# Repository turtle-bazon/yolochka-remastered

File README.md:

# Yolochka Remastered

Yolochka Remastered is a 36 keys (3x5 + 3 thumbs per hand) row staggered keyboard, inspired by [Aroum's YOLOCHKA](https://github.com/aroum/yolochka). It started as an attempt to turn the original YOLOCHKA into a PCB-based design.

## Images

## PCB Images

## Bill Of Materials

| Item                       | Quantity | Remarks                                                   |
| ---------------------------|----------| ----------------------------------------------------------|
| NRFproMicro                | 1        | [Link](https://aliexpress.com/item/1005007088422530.html) |
| MX Style Mechanical Switch | 36       | Any green themed colors, but works any, see below         |
| MX HotSwap Socket          | 36       | Any MX Compatible, but green preferred                    |
| SMD Diode 1n4148 SOD123    | 36       | If you can find green or red is good                      |
| SK6812MINI-E               | 41       |                                                           |
| MSK12C02                   | 1        | Power switch                                              |
| EVQP7C01K                  | 1        | Reset switch                                              |
| 14500 li-ion battery       | 2        |                                                           |
| 24 AWG wire                |          | Or something similar                                      |
| M2 threaded insert         | 11       | 3mm, OD 3.2mm                                             |
| M2x4 Countersunk head      | 2        | For led panel                                             |
| M2x10 Countersunk head     | 4        | For PCB                                                   |
| M2x5 Countersunk head      | 7        | For Case                                                  |

## Firmware

My zmk repo is available [here](https://github.com/turtle-bazon/zmk-yolochka-remastered)

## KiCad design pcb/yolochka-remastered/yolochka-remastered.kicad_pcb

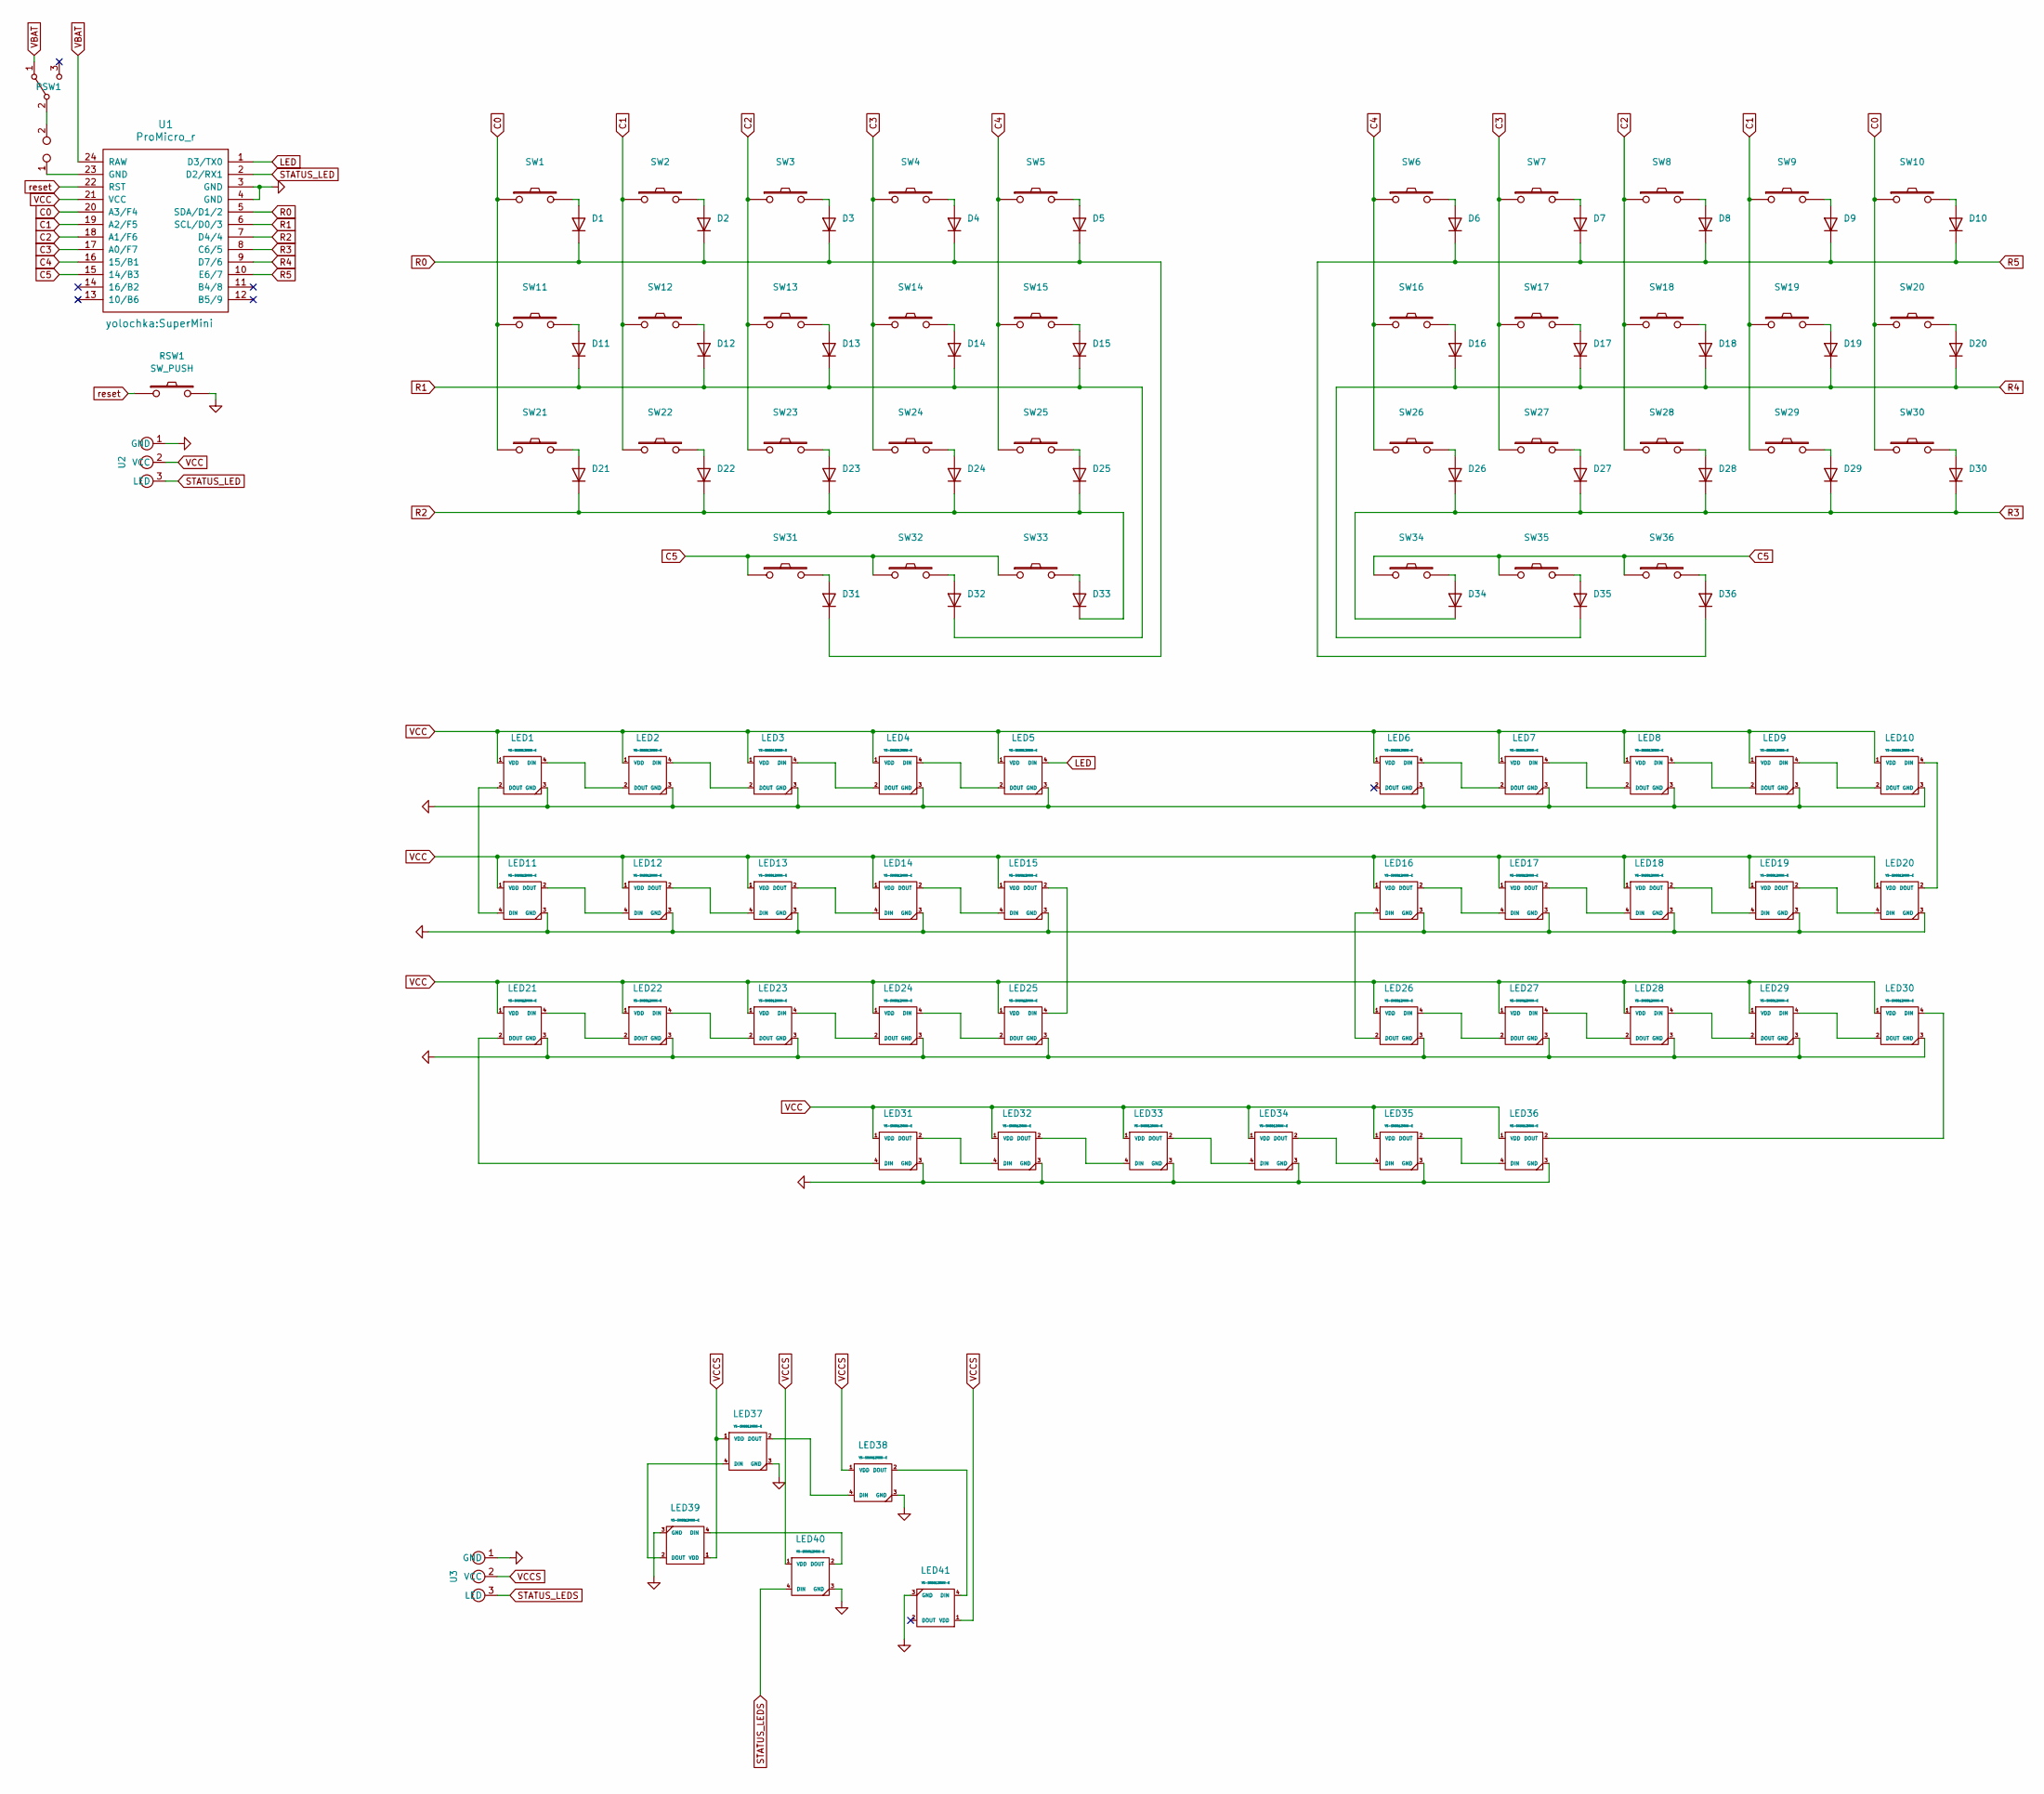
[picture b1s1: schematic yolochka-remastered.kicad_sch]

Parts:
D1, D2, D3, D4, D5, D6, D7, D8, D9, D10, D11, D12, D13, D14, D15, D16, D17, D18, D19, D20, D21, D22, D23, D24, D25, D26, D27, D28, D29, D30, D31, D32, D33, D34, D35, D36: 1N4148; D3_SMD_single
LED1, LED2, LED3, LED4, LED5, LED6, LED7, LED8, LED9, LED10, LED11, LED12, LED13, LED14, LED15, LED16, LED17, LED18, LED19, LED20, LED21, LED22, LED23, LED24, LED25, LED26, LED27, LED28, LED29, LED30, LED31, LED32, LED33, LED34, LED35, LED36, LED37, LED38, LED39, LED40, LED41: YS-SK6812MINI-E; YS-SK6812MINI-E_single
PSW1: SW_SPDT; MSK-12C02
RSW1: SW_PUSH; SW_EVQP7C01K
SW1, SW2, SW3, SW4, SW5, SW6, SW7, SW8, SW9, SW10, SW11, SW12, SW13, SW14, SW15, SW16, SW17, SW18, SW19, SW20, SW21, SW22, SW23, SW24, SW25, SW26, SW27, SW28, SW29, SW30, SW31, SW32, SW33, SW34, SW35, SW36: SW_PUSH; MX-single
TP1: TestPoint_2Pole; battery_conn_duplex
U1: ProMicro_r; SuperMini
U2, U3: rgb3pin

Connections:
C0: SW1.1, SW10.1, SW11.1, SW20.1, SW21.1, SW30.1, U1.20 (A3/F4)
C1: SW2.1, SW9.1, SW12.1, SW19.1, SW22.1, SW29.1, U1.19 (A2/F5)
C2: SW3.1, SW8.1, SW13.1, SW18.1, SW23.1, SW28.1, U1.18 (A1/F6)
C3: SW4.1, SW7.1, SW14.1, SW17.1, SW24.1, SW27.1, U1.17 (A0/F7)
C4: SW5.1, SW6.1, SW15.1, SW16.1, SW25.1, SW26.1, U1.16 (15/B1)
C5: SW31.1, SW32.1, SW33.1, SW34.1, SW35.1, SW36.1, U1.15 (14/B3)
GND: LED1.3 (GND), LED2.3 (GND), LED3.3 (GND), LED4.3 (GND), LED5.3 (GND), LED6.3 (GND), LED7.3 (GND), LED8.3 (GND), LED9.3 (GND), LED10.3 (GND), LED11.3 (GND), LED12.3 (GND), LED13.3 (GND), LED14.3 (GND), LED15.3 (GND), LED16.3 (GND), LED17.3 (GND), LED18.3 (GND), LED19.3 (GND), LED20.3 (GND), LED21.3 (GND), LED22.3 (GND), LED23.3 (GND), LED24.3 (GND), LED25.3 (GND), LED26.3 (GND), LED27.3 (GND), LED28.3 (GND), LED29.3 (GND), LED30.3 (GND), LED31.3 (GND), LED32.3 (GND), LED33.3 (GND), LED34.3 (GND), LED35.3 (GND), LED36.3 (GND), RSW1.2, U1.3 (GND), U1.4 (GND), U2.1 (GND)
GNDS: LED37.3 (GND), LED38.3 (GND), LED39.3 (GND), LED40.3 (GND), LED41.3 (GND), U3.1 (GND)
LED: LED5.4 (DIN), U1.1 (D3/TX0)
unnamed: D1.2 (A), SW1.2
unnamed: D2.2 (A), SW2.2
unnamed: D3.2 (A), SW3.2
unnamed: D4.2 (A), SW4.2
unnamed: D5.2 (A), SW5.2
unnamed: D6.2 (A), SW6.2
unnamed: D7.2 (A), SW7.2
unnamed: D8.2 (A), SW8.2
unnamed: D9.2 (A), SW9.2
unnamed: D10.2 (A), SW10.2
unnamed: D11.2 (A), SW11.2
unnamed: D12.2 (A), SW12.2
unnamed: D13.2 (A), SW13.2
unnamed: D14.2 (A), SW14.2
unnamed: D15.2 (A), SW15.2
unnamed: D16.2 (A), SW16.2
unnamed: D17.2 (A), SW17.2
unnamed: D18.2 (A), SW18.2
unnamed: D19.2 (A), SW19.2
unnamed: D20.2 (A), SW20.2
unnamed: D21.2 (A), SW21.2
unnamed: D22.2 (A), SW22.2
unnamed: D23.2 (A), SW23.2
unnamed: D24.2 (A), SW24.2
unnamed: D25.2 (A), SW25.2
unnamed: D26.2 (A), SW26.2
unnamed: D27.2 (A), SW27.2
unnamed: D28.2 (A), SW28.2
unnamed: D29.2 (A), SW29.2
unnamed: D30.2 (A), SW30.2
unnamed: D31.2 (A), SW31.2
unnamed: D32.2 (A), SW32.2
unnamed: D33.2 (A), SW33.2
unnamed: D34.2 (A), SW34.2
unnamed: D35.2 (A), SW35.2
unnamed: D36.2 (A), SW36.2
unnamed: LED1.4 (DIN), LED2.2 (DOUT)
unnamed: LED1.2 (DOUT), LED11.4 (DIN)
unnamed: LED2.4 (DIN), LED3.2 (DOUT)
unnamed: LED3.4 (DIN), LED4.2 (DOUT)
unnamed: LED4.4 (DIN), LED5.2 (DOUT)
unnamed: LED6.4 (DIN), LED7.2 (DOUT)
unnamed: LED7.4 (DIN), LED8.2 (DOUT)
unnamed: LED8.4 (DIN), LED9.2 (DOUT)
unnamed: LED10.4 (DIN), LED20.2 (DOUT)
unnamed: LED9.4 (DIN), LED10.2 (DOUT)
unnamed: LED11.2 (DOUT), LED12.4 (DIN)
unnamed: LED12.2 (DOUT), LED13.4 (DIN)
unnamed: LED13.2 (DOUT), LED14.4 (DIN)
unnamed: LED14.2 (DOUT), LED15.4 (DIN)
unnamed: LED15.2 (DOUT), LED25.4 (DIN)
unnamed: LED16.4 (DIN), LED26.2 (DOUT)
unnamed: LED16.2 (DOUT), LED17.4 (DIN)
unnamed: LED17.2 (DOUT), LED18.4 (DIN)
unnamed: LED18.2 (DOUT), LED19.4 (DIN)
unnamed: LED19.2 (DOUT), LED20.4 (DIN)
unnamed: LED21.4 (DIN), LED22.2 (DOUT)
unnamed: LED21.2 (DOUT), LED31.4 (DIN)
unnamed: LED22.4 (DIN), LED23.2 (DOUT)
unnamed: LED23.4 (DIN), LED24.2 (DOUT)
unnamed: LED24.4 (DIN), LED25.2 (DOUT)
unnamed: LED26.4 (DIN), LED27.2 (DOUT)
unnamed: LED27.4 (DIN), LED28.2 (DOUT)
unnamed: LED28.4 (DIN), LED29.2 (DOUT)
unnamed: LED29.4 (DIN), LED30.2 (DOUT)
unnamed: LED30.4 (DIN), LED36.2 (DOUT)
unnamed: LED31.2 (DOUT), LED32.4 (DIN)
unnamed: LED32.2 (DOUT), LED33.4 (DIN)
unnamed: LED33.2 (DOUT), LED34.4 (DIN)
unnamed: LED34.2 (DOUT), LED35.4 (DIN)
unnamed: LED35.2 (DOUT), LED36.4 (DIN)
unnamed: LED37.4 (DIN), LED39.2 (DOUT)
unnamed: LED37.2 (DOUT), LED38.4 (DIN)
unnamed: LED38.2 (DOUT), LED41.4 (DIN)
unnamed: LED39.4 (DIN), LED40.2 (DOUT)
unnamed: PSW1.2 (B), TP1.2
unnamed: TP1.1, U1.23 (GND)
R0: D1.1 (K), D2.1 (K), D3.1 (K), D4.1 (K), D5.1 (K), D31.1 (K), U1.5 (SDA/D1/2)
R1: D11.1 (K), D12.1 (K), D13.1 (K), D14.1 (K), D15.1 (K), D32.1 (K), U1.6 (SCL/D0/3)
R2: D21.1 (K), D22.1 (K), D23.1 (K), D24.1 (K), D25.1 (K), D33.1 (K), U1.7 (D4/4)
R3: D26.1 (K), D27.1 (K), D28.1 (K), D29.1 (K), D30.1 (K), D34.1 (K), U1.8 (C6/5)
R4: D16.1 (K), D17.1 (K), D18.1 (K), D19.1 (K), D20.1 (K), D35.1 (K), U1.9 (D7/6)
R5: D6.1 (K), D7.1 (K), D8.1 (K), D9.1 (K), D10.1 (K), D36.1 (K), U1.10 (E6/7)
STATUS_LED: U1.2 (D2/RX1), U2.3 (LED)
STATUS_LEDS: LED40.4 (DIN), U3.3 (LED)
VBAT: PSW1.1 (A), U1.24 (RAW)
VCC: LED1.1 (VDD), LED2.1 (VDD), LED3.1 (VDD), LED4.1 (VDD), LED5.1 (VDD), LED6.1 (VDD), LED7.1 (VDD), LED8.1 (VDD), LED9.1 (VDD), LED10.1 (VDD), LED11.1 (VDD), LED12.1 (VDD), LED13.1 (VDD), LED14.1 (VDD), LED15.1 (VDD), LED16.1 (VDD), LED17.1 (VDD), LED18.1 (VDD), LED19.1 (VDD), LED20.1 (VDD), LED21.1 (VDD), LED22.1 (VDD), LED23.1 (VDD), LED24.1 (VDD), LED25.1 (VDD), LED26.1 (VDD), LED27.1 (VDD), LED28.1 (VDD), LED29.1 (VDD), LED30.1 (VDD), LED31.1 (VDD), LED32.1 (VDD), LED33.1 (VDD), LED34.1 (VDD), LED35.1 (VDD), LED36.1 (VDD), U1.21 (VCC), U2.2 (VCC)
VCCS: LED37.1 (VDD), LED38.1 (VDD), LED39.1 (VDD), LED40.1 (VDD), LED41.1 (VDD), U3.2 (VCC)
reset: RSW1.1, U1.22 (RST)

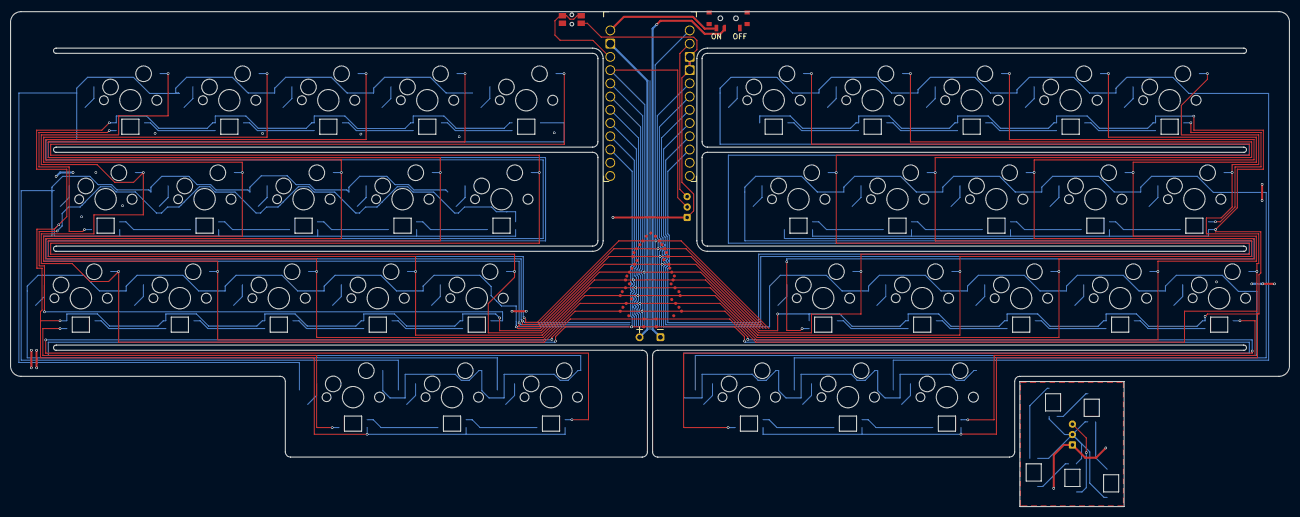
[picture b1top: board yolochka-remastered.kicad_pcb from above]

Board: 2 copper layers, 245.5 x 95.0 mm, 119 parts (0 on the bottom side), 98 nets.

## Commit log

2025-07-22 Initial routing
2025-08-02 Change led position and initial reroute
2025-09-23 Initial route
2025-09-29 Mostly routed
2025-09-29 Switches routed, rgb led almost
2025-09-30 Elements added, alsmost full routed
2025-10-09 All things routed
2025-10-10 PCB prepared
2025-10-10 Prepared for release
2025-10-15 Version 0.2 with cuts for mount colons
2025-10-15 Removed production files
2025-10-15 Ignore production files
2026-01-05 Additional materials
2026-01-16 Rotate rgb pins texts
2026-01-16 Case source and exports
2026-01-17 Added silicone molds and some helpers
2026-01-17 Fix battery pads
2026-01-17 Slightly increased tolerances for battery cuts in bottom
2026-01-17 Slightly increased tolerances for battery cuts in bottom (source files)
2026-01-19 Readme initial
2026-01-19 Fixes of readme
2026-01-19 Fixes of screw heads
2026-01-19 Removed license in readme as it available in repo
2026-01-22 Added tented bottom
